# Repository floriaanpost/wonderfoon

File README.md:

<meta name="google-site-verification" content="D2DzTi8eTN-HyuHSnyPzxfvAiq60_1QDBox8yPDGH7g" />

# V3 is klaar!
Omdat ik zelf ook weer plezier kreeg in het project heb ik v3 gemaakt. Helaas (nog) geen DTMF, maar wel betere stabiliteit (minder vaak/nooit fouten met pulsen tellen) en makkelijker om de firmware te updaten (ISCP port). Ook zit er een LED op het board voor debugging (of om te laten zien dat hij aan staat).

Ik hoop dat het met deze versie gemakkelijker en leuker wordt voor mensen om te experimenteren met de code en het precies zo te maken als je zelf wil.

Heb je nog een oude versie, dan kun je wel de firmware gebruiken van v3 (alleen in wonderfoon.ino moet je OLD_PIN_CONFIG uncommenten), of anders kun je alles van v2 nog terugvinden in de v2 branch.

Verder valt het mij op dat mensen het lastig vinden om de Attiny te programmeren. Mocht dit je tegenhouden dan kan ik eventueel ook voorgeprogrammeerde chips opsturen, en vaak heb ik ook nog wel andere onderdelen liggen, en als je heel graag een wonderfoon wil, maar je kunt niet solderen, dan wil ik er misschien zelfs wel een voor je in elkaar solderen. Vraag even naar de mogelijkheden op de mail :)

# Wonderfoon mini
De Wonderfoon is een ouderwetse draaischijftelefoon waar je muziek te horen krijgt door de hoorn als je een nummer draait. Het is oorspronkelijk bedacht als "speelgoed" voor (demente) ouderen door Leo Willems. De ouderwetse telefoon uit hun jonge jaren, gecombineerd met muziek uit dezelfde tijd is vaak en leuke ervaring voor ouderen. Het oorspronkelijke idee is gemaakt met een Raspberry Pi (een soort kleine computer). Voor het oorspronkelijke plan moet de telefoon (onherstelbaar) gesloopt worden. Met inspiratie van [een project van Jan Derogee (TeleJukebox)](https://github.com/JanDerogee/TeleJukebox) heb ik een nieuw type Wonderfoon ontworpen. Hierbij hoeft de telefoon niet gesloopt te worden en kun je de stekker van de telefoon gemakkelijk in een doosje stoppen dat zich gedraagt als de telefooncentrale. Ook is de Raspberry Pi vervangen door een kleine mp3 speler (DFPlayer Mini) en een microcontroller (ATTiny85).

Ik krijg vaak soortgelijke vragen door mensen die de wonderfoon aan het bouwen zijn, onderaan deze pagina staat een FAQ sectie, lees die graag eerst voor je een vraag aan mij stuurt. Die beantwoord ik graag, maar ik houd ook erg van mijn weekend :)

# Foto's
De complete wonderfoon is in een klein doosje gestopt wat een standaard doosje is dat gemaakt wordt door Kopp en Q-link. Het printpaatje is zo ontworpen dat het precies past.

Als je het doosje openschroeft zie je het volgende:

Er is een speciaal printplaatje ontworpen die precies in het doosje past.

# Ik wil er een bouwen
In het bestand Bouwhandleiding Wonderfoon staat een handleiding van hoe je er een kunt solderen en programmeren. Met de gerberfiles kun je een printplaat bestellen. Let er goed op bij het bestellen dat je controleert of het midden ook echt een gat wordt voor je de bestelling plaatst. Ik heb ook nog behoorlijk wat printplaatjes liggen, dus je kunt ze ook bij mij bestellen.

# Componentenlijst
Ik kreeg de vraag waar je de componenten kunt kopen. Hieronder een voorbeeld. Dit is zonder enige twijfel niet de goedkoopste optie, maar het kan je in ieder geval helpen met de juiste componenten vinden:

- Attiny85: https://opencircuit.nl/Product/ATtiny85-DIP8
- DFPlayer mini: https://opencircuit.nl/Product/DFPlayer-Een-mini-mp3-speler-voor-Arduino
- Header pins (ICSP): https://opencircuit.nl/Product/Male-header-2x40-2.54mm-zwart
- USB type B connector: https://www.conrad.nl/p/econ-connect-usbbu1bn-usb-connector-bus-inbouw-horizontaal-wit-1-stuks-1883654
- 10 uF elco: https://opencircuit.nl/Product/10uF-35V-Condensator-elektrolytisch
- 1 uF elco: https://opencircuit.nl/Product/1uF-450V-Condensator-elektrolytisch
- LED (optioneel): https://opencircuit.nl/Product/Rood-5mm-diffuse-LED-10-stuks
- 10 kOhm weerstand: https://opencircuit.nl/Product/10K%CE%A9-Metaalfilm-weerstand-1-4W-10-stuks
- 220 Ohm weerstand: https://opencircuit.nl/Product/220%CE%A9-Metaalfilm-weerstand-1-4W-10-stuks
- 2.7 kOhm (dit is 2kOhm, maar dat is ook wel prima): https://opencircuit.nl/Product/2K%CE%A9-Metaalfilm-weerstand-1-4W-10-stuks
- Telefooncontactdoos https://www.gamma.nl/assortiment/q-link-telefoon-contactdoos-opbouw-modulair-4-polig-wit/p/B547149

# De liedjes nummeren is veel moeite...
Hier heeft Daan een python scriptje voor gemaakt dat je kunt gebruiken:
https://github.com/daanv98/mp3nu

Je kunt ook file renamer gebruiken:
http://www.sherrodcomputers.com/products_filerenamer.cfm

# FAQ
Ik krijg vaak soortgelijke vragen die ik hieronder zal beantwoorden:

#### Hoe moet ik de bestanden op de SD kaart zetten (lees dit sowieso even door, dit zorgt voor het meest problemen)
De DFplayer mini is een handig en goedkoop stukje hardware, maar heeft een paar vreemde eigenschappen, waar je rekening mee moet houden als je bestanden op de SD kaart zet. Met de onderstaande stappen gaat het (bij mij althans) altijd goed:

- Formatteer de SD kaart (FAT)
- Zet eerst de 01/ map erop (https://github.com/floriaanpost/wonderfoon/tree/master/muziek). Dit mapje bevat de kiestoon die je hoort als je de hoorn van de haak neemt en de verbinding verbroken toon en nog wat zaken. Het is van cruciaal belang dat je dit eerst doet voor dat je iets met een MP3 map doet. Dit komt omdat de DFPlayer mini de nummering doet op basis van de volgorde waarop de liedjes op de SD kaart zijn gezet, dus die moeten als aller eerst op de SD kaart worden gezet.
- Maak hierna een mapje genaamd MP3 in de hoofdmap. Zet hierin liedjes op volgorde genummerd, startend met precies 4 cijfers. Alleen de eerste vier cijfers maken uit, daarna kun je alles schrijven wat je wil. Dit nummeren is veel werk, dus daarvoor kun je eventueel het Python scriptje van Daan gebruiken (zie hierboven), of zelf een bash-kunstwerktje maken, of gewoon handmatig te werk gaan. Let op dat er geen gaten zitten in de nummering! Zie als voorbeeld: https://github.com/floriaanpost/wonderfoon/tree/master/muziek/MP3
- Laat hierna de 01 map voor altijd met rust, je kunt wel dingen aanpassen in de MP3 map, maar let op dat er geen verborgen bestanden ontstaan op de SD kaart, die ziet de DFPlayer mini niet als verborgen bestanden, en dat kan zorgen voor vreemde problemen.

Als je een mac hebt (ik ben zelf zo'n persoon) heb je een beetje een probleem. Mac is heel gretig in het produceren van verborgen bestanden en hele trash mappen op sd kaarten. Het is mij maar zelden gelukt om het daar goed te doen. Ik pak nu altijd mijn Linux laptop, wat verreweg het beste gaat op dit gebied. Windows zorgt ook voor weinig problemen.

#### Ik heb de bestanden precies zoals hierboven op mijn SD kaart gezet, en toch werkt het niet.
Ik heb iemand gehad die SD kaartjes had gekocht die ook ik niet aan de praat heb gekregen. We hebben nog steeds geen idee wat het probleem was. Ik heb vaak de allergoedkoopste Kingston SD kaart gebruikt die ik kon vinden en daar nog nooit problemen mee gehad. Geen idee dus wat dit precies kan zijn, maar een andere SD kaart proberen is geen slecht idee.

#### Ik denk dat mijn ATtiny85 niet goed is geprogrammeerd
Als de led op enig moment knippert, betekent dat hoogstwaarschijnlijk dat de ATtiny85 goed is geprogrammeerd, aangezien die de LED aanstuurt, als de LED dus knippert, zoek dan naar een andere oorzaak dan de ATtiny85. Doet de LED helemaal niets, dan is er een goede kans dat de ATtiny85 inderdaad niet goed is geprogrammeerd. 

#### De LED blijft knipperen, en de wonderfoon werkt niet
Zo lang de led knippert is de ATtiny85 bezig met verbinding maken met de kleine MP3 speler, de DFPLayer mini. Dit gaat zelden meteen goed zodra je hem in het stopcontact steekt, de DFPlayer heeft wat meer tijd nodig om op te starten dan de ATtiny85. Als het knipperen echter niet stopt, dan gaat er iets mis. Dit kan betekenen dat er geen SD kaart in de DFPlayer zit (maar ik ga ervan uit dat jullie dat niet vergeten), of dat er iets is waardoor de bestanden op de SD kaart niet goed gelezen kunnen worden, zie het eerste punt over hoe je bestanden op de SD kaart moet zetten, en het tweede punt over sommige SD kaarten die niet werken.

#### Ik hoor bijvoorbeeld de "verkeerd verbonden" toon als ik de hoorn opneem in plaats van de kiestoon, of meteen een liedje
Zet de liedjes juist op de SD kaart, zoals beschreven in het eerste punt. Als je een mac hebt, probeer een windows/linux computer te vinden en probeer het daarmee, of zoek uit hoe het wel lukt op een mac en vertel het mij ;)

#### Ik wil de ATtiny85 programmeren met een Arduino, maar het lukt me niet
Een USBasp is veel makkelijker om te programmeren, en heel goedkoop, maar als je het toch met een arduino wil doen kun je deze handleiding volgen:
https://create.arduino.cc/projecthub/arjun/programming-attiny85-with-arduino-uno-afb829
Er is alleen een ding dat hier niet vermeld staat en dat is dat wanneer je de "ArduinoISP" sketch op de arduino zet je regel 81 moet uncommenten (// #define USE_OLD_STYLE_WIRING). Verder is gebruik ik een kloksnelheid van 1MHz voor de attiny (hoewel hoger ook zou moeten werken).

#### De sketch compileert niet bij het programmeren. 
Je moet de attiny eerst toevoegen aan de arduino IDE.
Volg de instructies van deze repository: https://github.com/damellis/attiny

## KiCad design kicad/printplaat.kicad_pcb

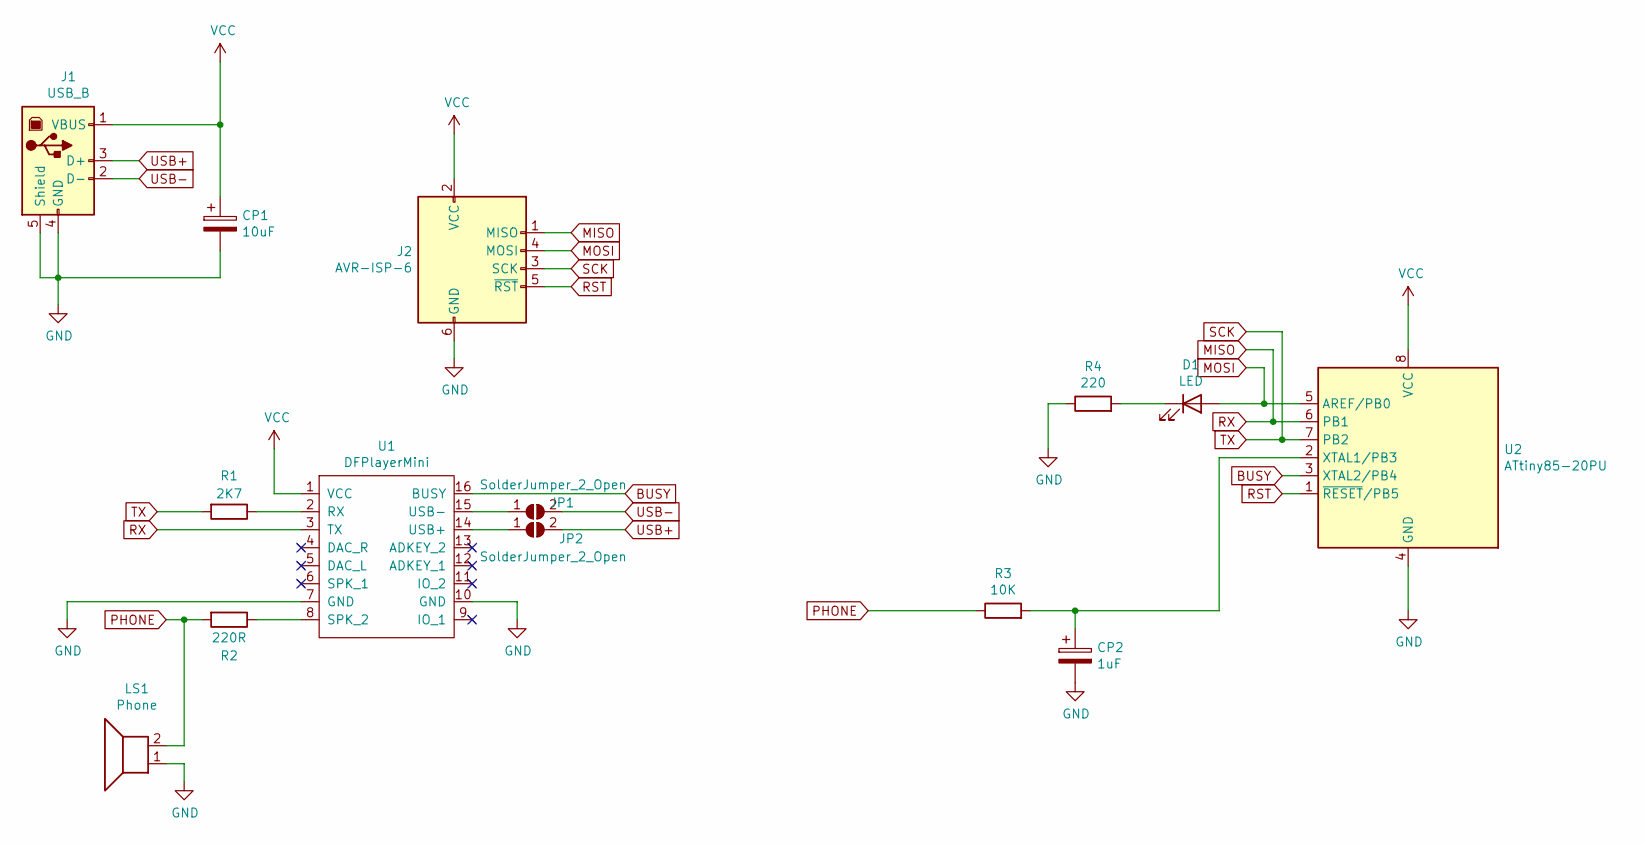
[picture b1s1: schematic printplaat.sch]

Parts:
CP1: 10uF; CP_Radial_D5.0mm_P2.50mm
CP2: 1uF; CP_Radial_D5.0mm_P2.50mm
D1: LED; LED_D5.0mm
J1: USB_B; USB_B_OST_USB-B1HSxx_Horizontal
J2: AVR-ISP-6; PinHeader_2x03_P2.54mm_Vertical
JP1, JP2: SolderJumper_2_Open; SolderJumper-2_P1.3mm_Open_RoundedPad1.0x1.5mm
LS1: Phone; PinHeader_2x01_P2.54mm_Vertical
R1: 2K7; R_Axial_DIN0207_L6.3mm_D2.5mm_P10.16mm_Horizontal
R2: 220R; R_Axial_DIN0207_L6.3mm_D2.5mm_P10.16mm_Horizontal
R3: 10K; R_Axial_DIN0207_L6.3mm_D2.5mm_P10.16mm_Horizontal
R4: 220; R_Axial_DIN0207_L6.3mm_D2.5mm_P10.16mm_Horizontal
U1: DFPlayerMini; DFPlayer_Mini
U2: ATtiny85-20PU; DIP-8_W7.62mm

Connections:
BUSY: U1.16 (BUSY), U2.3 (XTAL2/PB4)
GND: CP1.2, CP2.2, J1.4 (GND), J1.5 (Shield), J2.6 (GND), LS1.1, R4.1, U1.7 (GND), U1.10 (GND), U2.4 (GND)
MISO: J2.1 (MISO), U1.3 (TX), U2.6 (PB1)
MOSI: D1.2 (A), J2.4 (MOSI), U2.5 (AREF/PB0)
unnamed: CP2.1, R3.2, U2.2 (XTAL1/PB3)
unnamed: D1.1 (K), R4.2
unnamed: JP1.1 (A), U1.15 (USB-)
unnamed: JP2.1 (A), U1.14 (USB+)
unnamed: R1.1, U1.2 (RX)
unnamed: R2.1, U1.8 (SPK_2)
PHONE: LS1.2, R2.2, R3.1
RST: J2.5 (~RST), U2.1 (~RESET~/PB5)
SCK: J2.3 (SCK), R1.2, U2.7 (PB2)
USB+: J1.3 (D+), JP2.2 (B)
USB-: J1.2 (D-), JP1.2 (B)
VCC: CP1.1, J1.1 (VBUS), J2.2 (VCC), U1.1 (VCC), U2.8 (VCC)

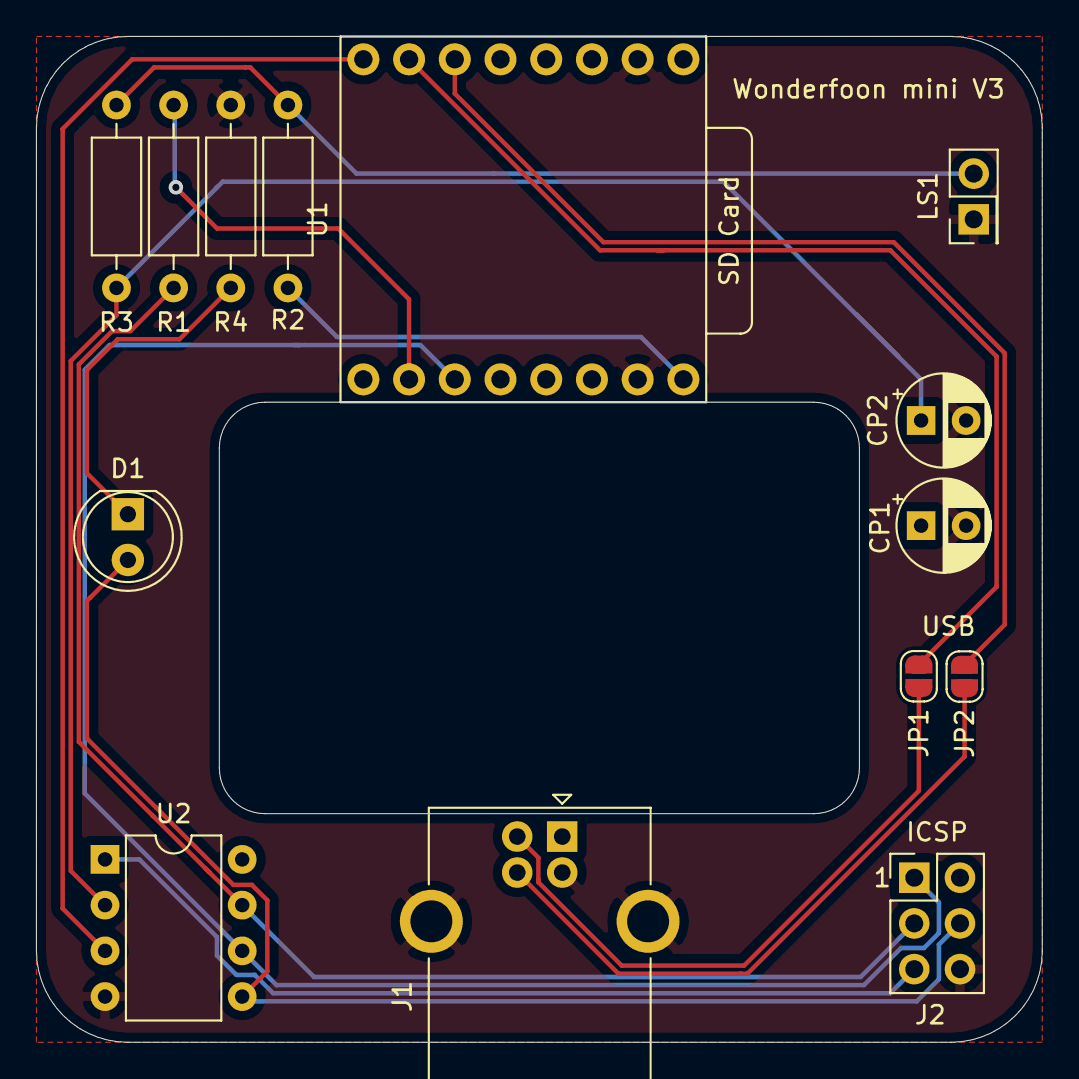
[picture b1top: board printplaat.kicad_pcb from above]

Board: 2 copper layers, 55.9 x 55.9 mm, 14 parts (0 on the bottom side), 16 nets.

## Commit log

2020-06-03 added dialtone/disconnected/wrong number mp3 files
2020-06-04 add new pcbs message
2020-06-04 changed images to latest version
2020-06-18 pcb and firmware v3
2020-06-18 updated manual
2020-06-18 updated gerber files
2020-06-25 Update README.md
    Componentenlijst toegevoegd.
2020-06-25 Made it easier for google to find project
2020-06-25 removed tracker file again
2020-06-26 removed debug=false from Phone.cpp
2020-06-30 fixed CP1 shown twice in manual
2020-08-15 Updated build manual
2021-01-03 add FAQ to readme
2021-01-16 added updated schema
